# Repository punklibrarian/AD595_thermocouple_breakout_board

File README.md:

AD595 Thermocouple Breakout Board
==================================
Copyright 2011 Design Tech Industries (DTI)

DTI email: <jameskun89@rocketmail.com>

The **AD595 Thermocouple Amplifier Breakout Board** is a a breakout board, or shield, for the ATtiny 45/85 Development Board. It 
is slightly specialised to be used with the SparkFun relay control board but should be usable for other purposes.

Features:

 * Open Source; OSHW compliant
 * Design files freely available

In this repository you will find the gerber files for BatchPCB (http://batchpcb.com) and DorkbotPDX (http://dorkbotpdx.org/wiki/pcb_order),
along with project (.pro), board (.brd) and schematic (.sch) files for the board in the 'EAGLE and 'KiCad' folders.

You can also find this design on BatchPCB ready to add to your cart: http://www.batchpcb.com/index.php/Products/73646

**This board will be under continual change and versions may not work the way they are supposed to. You have been warned**

INSTALLATION
------------
**EAGLE**
The design is saved as an EAGLE project. EAGLE PCB design software is available from www.cadsoftusa.com 
free for non-commercial use and can be installed on Windows and Mac, with Linux support through WINE. 
To use this project download it and place the directory containing these files into the "eagle" directory 
on your computer. Then open EAGLE and navigate to File -> Open -> AD595_thermocouple_breakout_board.sch

**KiCad**
KiCad EDA Suite is an Open Source alternative to EAGLE. It is available on Windows and Linux and can be installed 
on Mac. It is available from http://kicad.sourceforge.net and works in a similar way to EAGLE. You will find project 
files for KiCad in the aptly named folder in this repository. To use this project download it and place the directory 
containing these files into a folder of your choice. Then open KiCad and navigate to File -> Open -> 
'FOLDER_OF_YOUR_CHOICE' -> AD595_thermocouple_breakout_board.pro

BILL OF MATERIALS
-----------------

 * 1 x Analog Devices Thermocouple Type-K Amplifier - AD595 (http://littlebirdelectronics.com/products/thermocouple-amplifier-ad595aq)
 * 1 x 14-pin DIP Socket (http://littlebirdelectronics.com/products/dip-sockets-solder-tail-14pin-03)
 * 1 x Break Away Headers - Straight (http://littlebirdelectronics.com/products/break-away-headers-straight)
 * 1 x 3-pin Screw Terminal (http://littlebirdelectronics.com/products/screw-terminals-35mm-pitch-3pin)

DISTRIBUTION
------------
The specific terms of distribution of this project are governed by the license referenced below.

LICENSE
-------
> This work is licensed under the Creative Commons Attribution-ShareAlike License.  
> 
> To view a copy of this license, visit:
> 
>   http://creativecommons.org/licenses/by-sa/3.0/  
>   http://creativecommons.org/licenses/by-sa/3.0/legalcode
> 
> or send a letter to
> 
>   Creative Commons  
>   171 Second Street, Suite 300  
>   San Francisco  
>   California, 94105  
>   USA

The "license" folder within this repository also contains copies of the
license(s) referenced above.

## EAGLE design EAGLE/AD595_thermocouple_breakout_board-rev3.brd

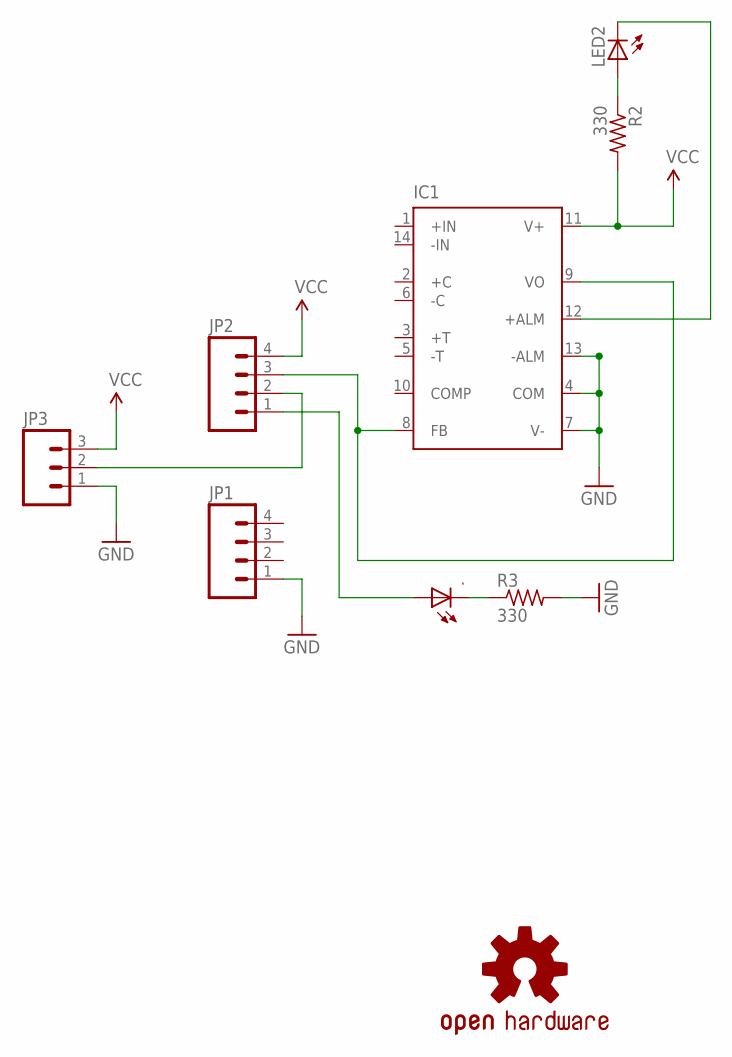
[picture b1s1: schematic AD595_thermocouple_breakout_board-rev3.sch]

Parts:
.: LED5MM
IC1: AD595; DIL14
JP1, JP2: M04LOCK; 1X04_LOCK
JP3: M03SCREW_LOCK; SCREWTERMINAL-3.5MM-3_LOCK.007S
LED2: LED5MM
R2, R3: 330; 0207/7
U$1: OSHW-LOGOS; OSHW-LOGO-S

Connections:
GND: IC1.4 (COM), IC1.7 (V-), IC1.13 (-ALM), JP1.1, JP3.1, R3.2
unnamed: JP2.2, JP3.2
unnamed: IC1.8 (FB), IC1.9 (VO), JP2.3
unnamed: ..K (C), R3.1
unnamed: ..A, JP2.1
unnamed: LED2.A, R2.1
unnamed: IC1.12 (+ALM), LED2.K (C)
VCC: IC1.11 (V+), JP2.4, JP3.3, R2.2

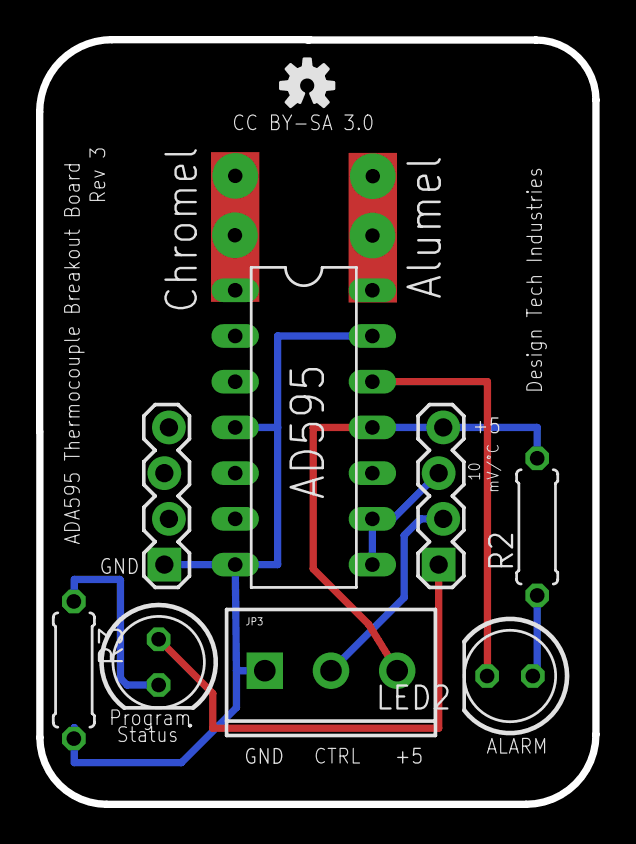
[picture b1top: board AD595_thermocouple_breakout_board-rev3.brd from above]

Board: 2 copper layers, 30.9 x 42.5 mm, 9 parts (0 on the bottom side), 8 nets.

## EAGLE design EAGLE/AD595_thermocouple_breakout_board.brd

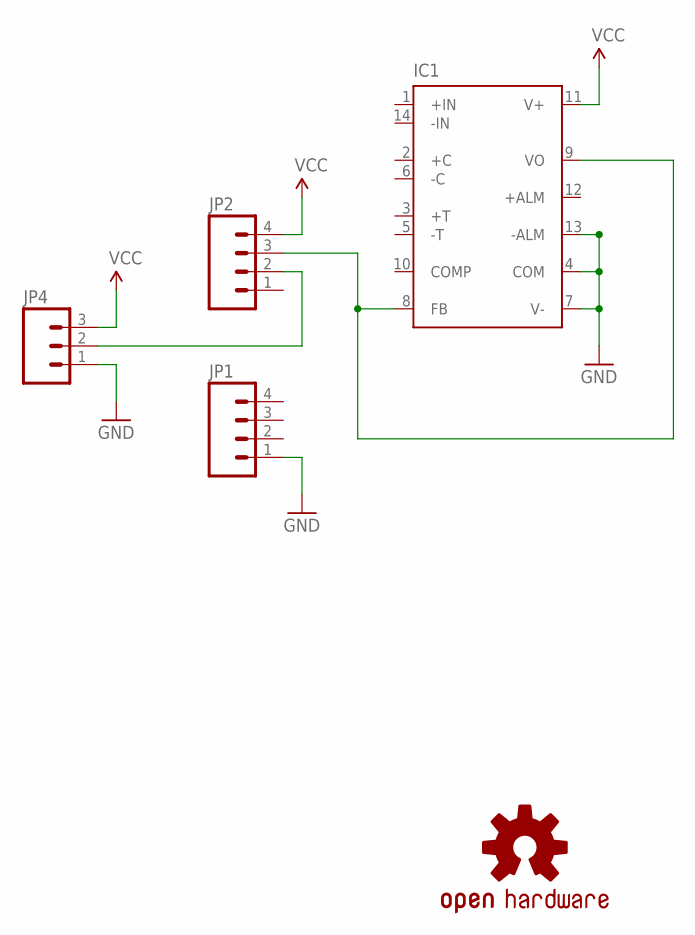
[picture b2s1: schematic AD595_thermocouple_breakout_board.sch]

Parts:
IC1: AD595; DIL14
JP1, JP2: M04LOCK; 1X04_LOCK
JP4: M03LOCK; 1X03_LOCK
U$1: OSHW-LOGOS; OSHW-LOGO-S

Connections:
GND: IC1.4 (COM), IC1.7 (V-), IC1.13 (-ALM), JP1.1, JP4.1
unnamed: JP2.2, JP4.2
unnamed: IC1.8 (FB), IC1.9 (VO), JP2.3
VCC: IC1.11 (V+), JP2.4, JP4.3

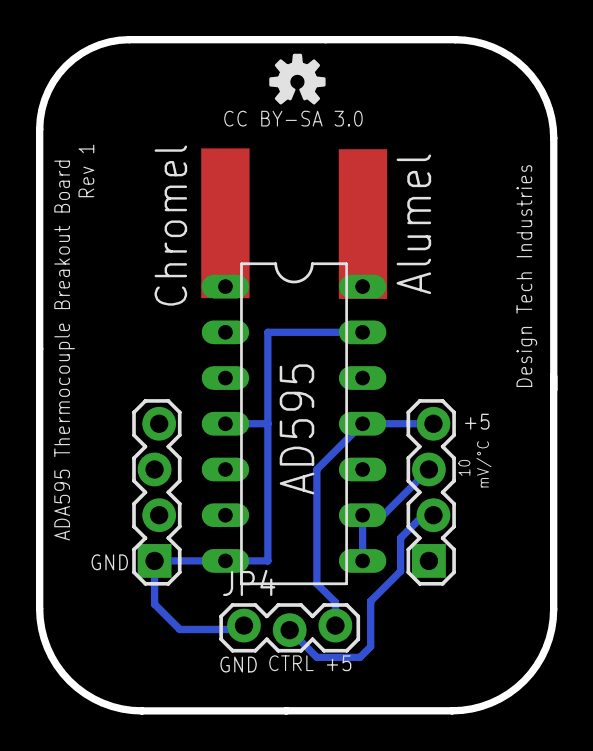
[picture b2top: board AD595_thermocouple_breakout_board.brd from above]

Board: 2 copper layers, 28.6 x 37.3 mm, 5 parts (0 on the bottom side), 4 nets.

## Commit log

2011-12-01 Initial commit of files.
2011-12-01 Added image of board exported from EAGLE.
2011-12-01 Commit of image of board exported from EAGLE.
2011-12-01 Commited image of board exported from EAGLE.
2011-12-13 Upgraded to EAGLE 6 and resaved files in new XML format.
2011-12-29 Added a Bill of Materials. Changes will be made once prototypes are made.
2012-07-23 Fix done to board, exposed copper for Thermocouple pads. Added an alarm LED and swapped right-angle headers with 3-pin screw terminal for control signal output.
2012-07-23 Fix made to Thermocouple solder pads.
    I thought I had the problem licked but I didn't. Had to end up throwing
    in two large pads per lead to get it to work. I might have to make an
    EAGLE library for the 'part' that'll do the job I need.
2012-07-23 Updated the BatchPCB gerber files to be inline with rev. 2 board design.
2012-07-24 Commit of revision three of board. Now includes a program status LED. This version is more part of a toaster reflow oven controller than anything else (hence keeping revision two active).
2012-07-24 Minor change to status LED and resistor in revision 3.

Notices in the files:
EAGLE/AD595_thermocouple_breakout_board-rev3.brd:
CC BY-SA 3.0
parts and their libraries:
SparkFun-Connectors: Licensing: CC v3.0 Share-Alike You are welcome to use this library for commercial purposes.
